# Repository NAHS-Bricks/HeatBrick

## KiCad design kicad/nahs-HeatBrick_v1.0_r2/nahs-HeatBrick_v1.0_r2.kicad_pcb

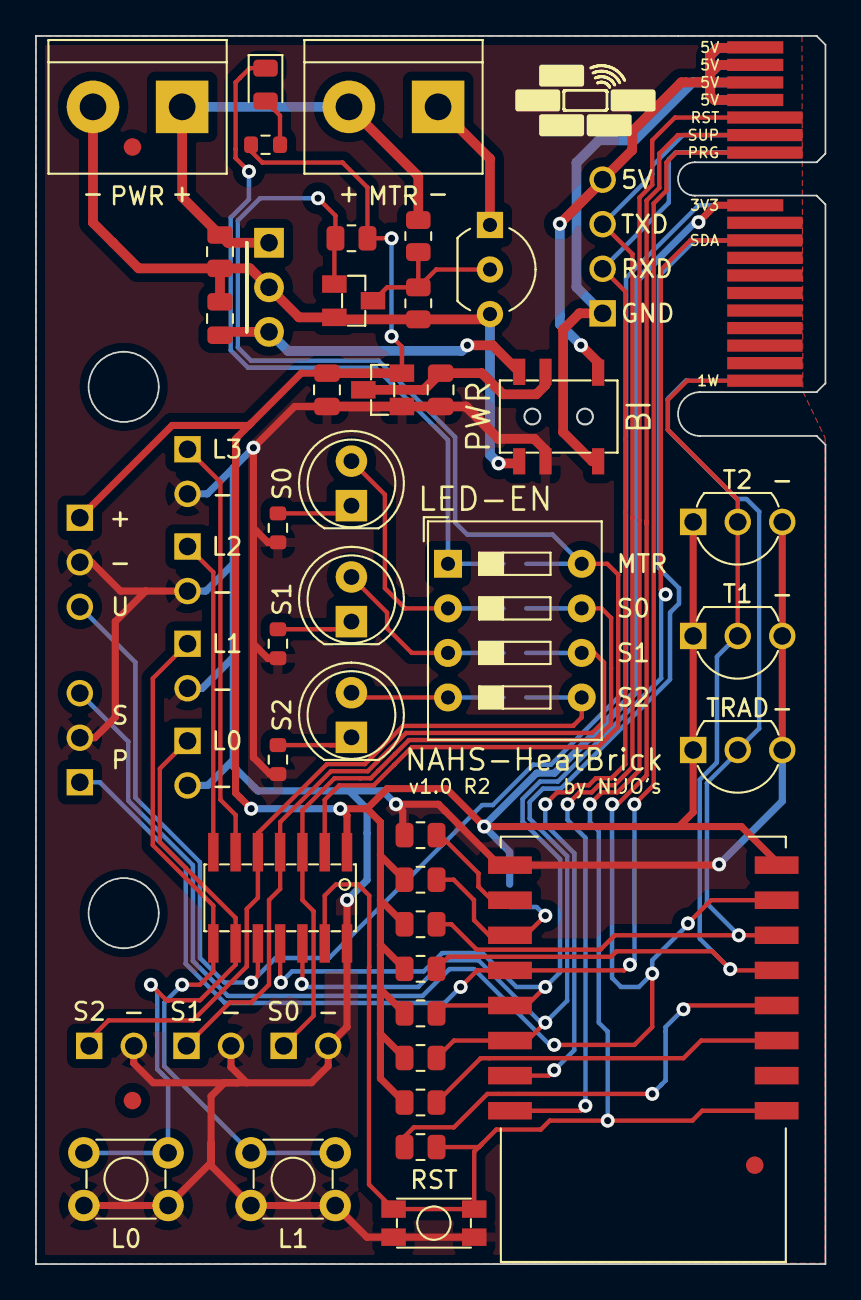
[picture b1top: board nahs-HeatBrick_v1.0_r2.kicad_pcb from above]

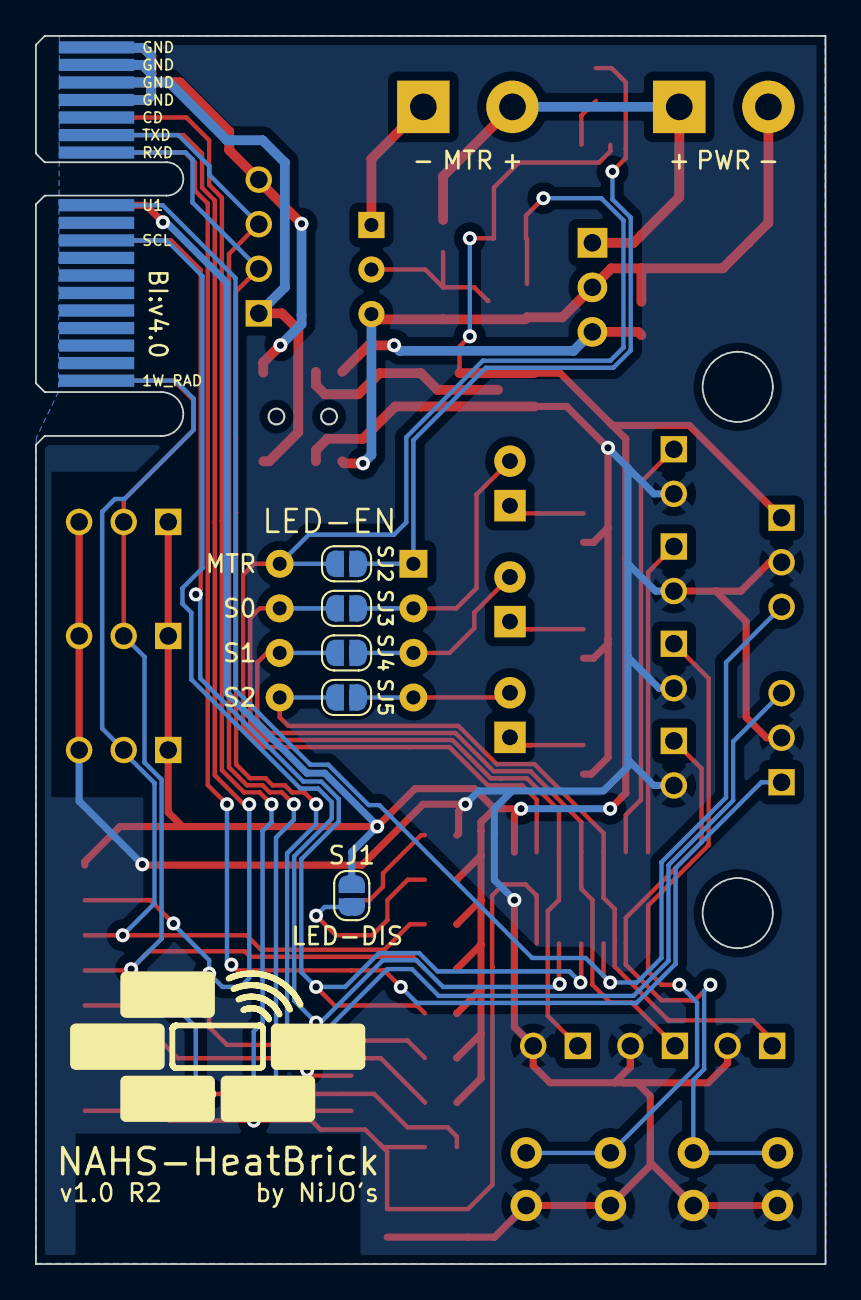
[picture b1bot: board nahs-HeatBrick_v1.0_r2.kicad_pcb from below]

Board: 2 copper layers, 45.0 x 70.0 mm, 60 parts (6 on the bottom side), 40 nets.

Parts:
C1, C1#2, C1#3, C1#4: 100nF; C_0805_2012Metric
FID1, FID2, FID3: Fiducial; Fiducial_1mm_Mask2mm
IC1: ESP12S
IC2: ATTINY414; SOIC14
J: Brick-Interface-V4; Brick_Interface_V4_inset
J2, J3: AKL 101-02; TerminalBlock_bornier-2_P5.08mm
JP1, JP5: PINHD_1X03; PINHD_1X03_2.54_1mm_Round
JP2: PINHD_1X04; PINHD_1X04_2.54_1mm_Round
JP3, JP4, JP6, JP10, JP11, JP12, JP13: PINHD_1x02; PINHD_1X02_2.54_1mm_Round
JP6#2, JP7, JP9: PINHD_1X03; PINHD_1X03_2.54_1mm_DS18B20
LED2: Red; LED_0805_2012Metric
LED3: Red; LED_D5.0mm
LED4: Green; LED_D5.0mm
LED5: Blue; LED_D5.0mm
LOGO1: brick_logo; x8mm
LOGO2: brick_logo; x17mm
Q1: BSS138; SOT23
Q3: BS170; TO-92_Inline_Wide
R1, R1#2, R5, R6: 3.9k; R_0805_2012Metric
R2: 1k; R_0805_2012Metric
R3, R4, R7, R9: 10k; R_0805_2012Metric
R10, R11: 130k; R_0805_2012Metric
R12, R13, R14, R15: 330; R_0603_1608Metric
SJ1, SJ1#2, SJ1#3, SJ1#4, SJ1#5: LED-DIS; SolderJumper-2_P1.3mm_Open_RoundedPad1.0x1.5mm
SW1: KMR_231_G_LFS
SW2: SSSS820101
SW3: SW_DIP_x04; SW_DIP_SPSTx04_Slide_9.78x12.34mm_W7.62mm_P2.54mm
SW4: Taster_3301; Taster_4545
SW5: Taster_4545
U1: MCP1700-3302; SOT23
U2: PXO7805-500-S

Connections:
1WIRE: IC1.5 (D5), J.B1 (UTIL1), JP6#2.2, JP7.2, R1#2.2
1W_RAD: IC1.6 (D6), J.A1 (UTIL5), JP9.2, R1.2
24+: C1#4.1, J2.1, J3.2, R10.2, U2.1 (VI)
24-: C1.2, C1#4.2, J2.2, Q1.2 (S), Q3.3 (S), R11.1, SW2.1, U2.2 (GND)
+3V3: C1#3.1, IC1.8 (VCC), IC2.1 (VCC), J.B11 (3.3V), JP5.1, JP6#2.1, JP7.1, JP9.1, R1.1, R1#2.1, R3.1, R4.1, R5.1, R6.1, R9.2, R12.1, SJ1#3.1 (A), U1.2 (VO)
BOOT1: IC1.17 (D4), R4.2, SJ1#3.2 (B)
BOOT2: IC1.16 (D8), R7.2
E1: IC2.2 (PA4), Q1.1 (G), R9.1, SJ1#2.1 (A), SW3.8
E2: IC2.3 (PA5), JP3.1, SJ1.1 (A), SW3.7
E3: IC2.4 (PA6), JP4.1, SJ1#5.1 (A), SW3.6
E4: IC2.5 (PA7), JP6.1, SJ1#4.1 (A), SW3.5
EN: IC1.3 (EN), R3.2
GND: C1#2.2, C1#3.2, IC1.15 (GND), IC2.14 (GND), JP1.2, JP3.2, JP4.2, JP5.2, JP6.2, JP6#2.3, JP7.3, JP9.3, JP10.2, JP11.2, JP12.2, JP13.2, R7.1, R13.1, R14.1, R15.1, SW1.1, SW1.2, SW2.2, SW4.3, SW4.4, SW5.3, SW5.4, U1.1 (GND)
IN+: J.B15 (5V), J.B16 (5V), J.B17 (5V), J.B18 (5V), JP2.4, SW2.4
IN-: J.A15 (GND), J.A16 (GND), J.A17 (GND), J.A18 (GND), JP2.1, SW2.3
L0: IC2.9 (PB0), JP10.1, SW4.1, SW4.2
L1: IC2.8 (PB1), JP11.1, SW5.1, SW5.2
L2: IC2.7 (PB2), JP12.1
L3: IC2.6 (PB3), JP13.1
unnamed: C1.1, SW2.6, U2.3 (VO)
unnamed: IC1.4 (D0), R2.1
unnamed: J3.1, Q3.1 (D)
unnamed: LED2.1 (K), SJ1#2.2 (B), SW3.1
unnamed: LED2.2 (A), R12.2
unnamed: LED3.1 (K), R13.2
unnamed: LED3.2 (A), SJ1.2 (B), SW3.2
unnamed: LED4.1 (K), R14.2
unnamed: LED4.2 (A), SJ1#5.2 (B), SW3.3
unnamed: LED5.1 (K), R15.2
unnamed: LED5.2 (A), SJ1#4.2 (B), SW3.4
unnamed: Q1.3 (D), Q3.2 (G), R10.1, R11.2
PROG: IC1.18 (D3), J.B12 (PROG), JP1.1
RST: IC1.1 (~RST), IC2.13 (PA3), J.B14 (RST), R2.2, SW1.3, SW1.4
RXD: IC1.21 (RXD0), J.A12 (RX), JP2.2
SCL: IC1.20 (D1), IC2.12 (PA2), J.A9 (SCL), R6.2
SDA: IC1.19 (D2), IC2.11 (PA1), J.B9 (SDA), R5.2
SEL+: C1#2.1, SW2.5, U1.3 (VI)
SETUP: IC1.7 (D7), J.B13 (SETUP), JP1.3
TXD: IC1.22 (TXD0), J.A13 (TX), JP2.3
UPDI: IC2.10 (RST/UPDI), J.A11 (UPDI1), JP5.3

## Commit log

2023-11-16 v1.0 R1 Board done
2023-11-21 v1.0 R1 ibom done
2023-11-27 v1.0 R2 Board started by removing first design flaw
2023-12-10 v1.0 R2 Board updated DS18B20 Footprint
2023-12-27 working version of firmware v1
2024-01-10 v1.0 R2 Board done
